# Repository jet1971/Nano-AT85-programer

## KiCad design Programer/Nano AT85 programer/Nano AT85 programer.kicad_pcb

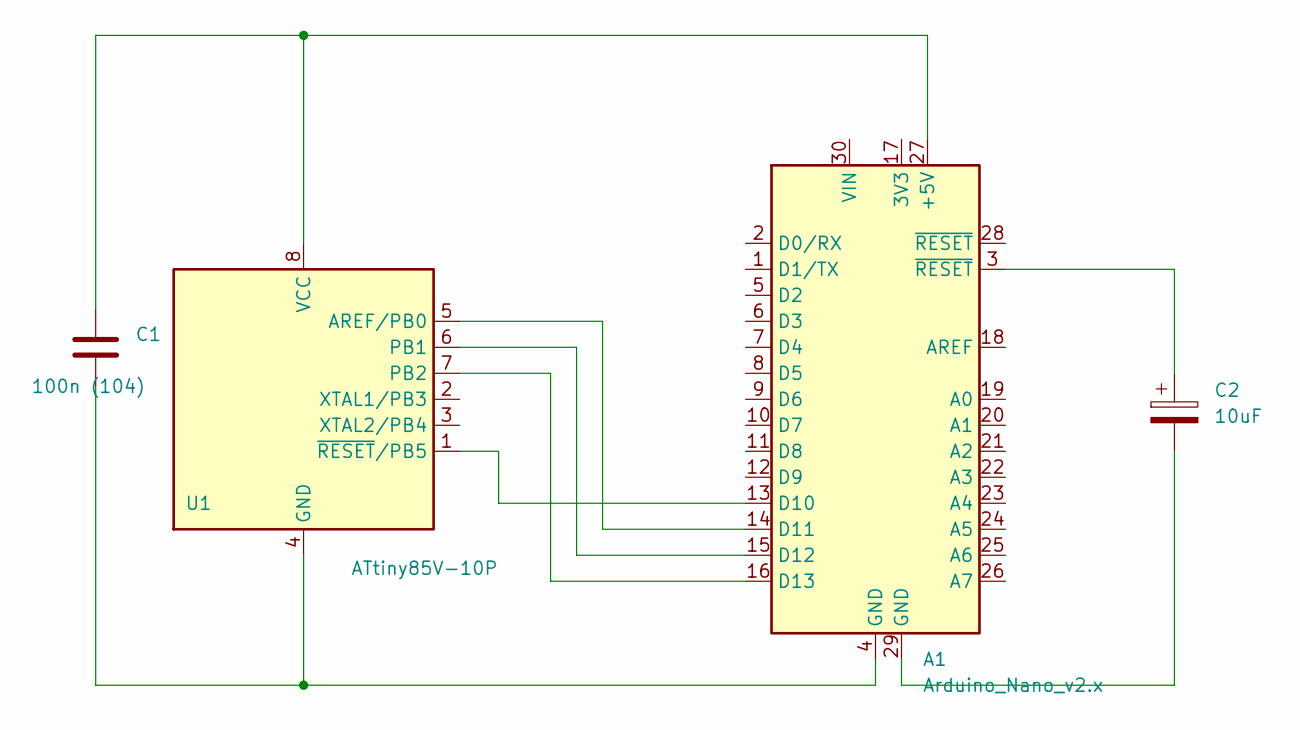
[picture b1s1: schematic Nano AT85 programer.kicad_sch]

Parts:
A1: Arduino_Nano_v2.x; Arduino_Nano
C1: 100n (104); C_Disc_D4.7mm_W2.5mm_P5.00mm
C2: 10uF; CP_Radial_D6.3mm_P2.50mm
U1: ATtiny85V-10P; DIP-8_W7.62mm

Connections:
unnamed: A1.3 (~RESET), C2.1
unnamed: A1.4 (GND), C1.2, U1.4 (GND)
unnamed: A1.13 (D10), U1.1 (~RESET/PB5)
unnamed: A1.14 (D11), U1.5 (AREF/PB0)
unnamed: A1.15 (D12), U1.6 (PB1)
unnamed: A1.16 (D13), U1.7 (PB2)
unnamed: A1.27 (+5V), C1.1, U1.8 (VCC)
unnamed: A1.29 (GND), C2.2

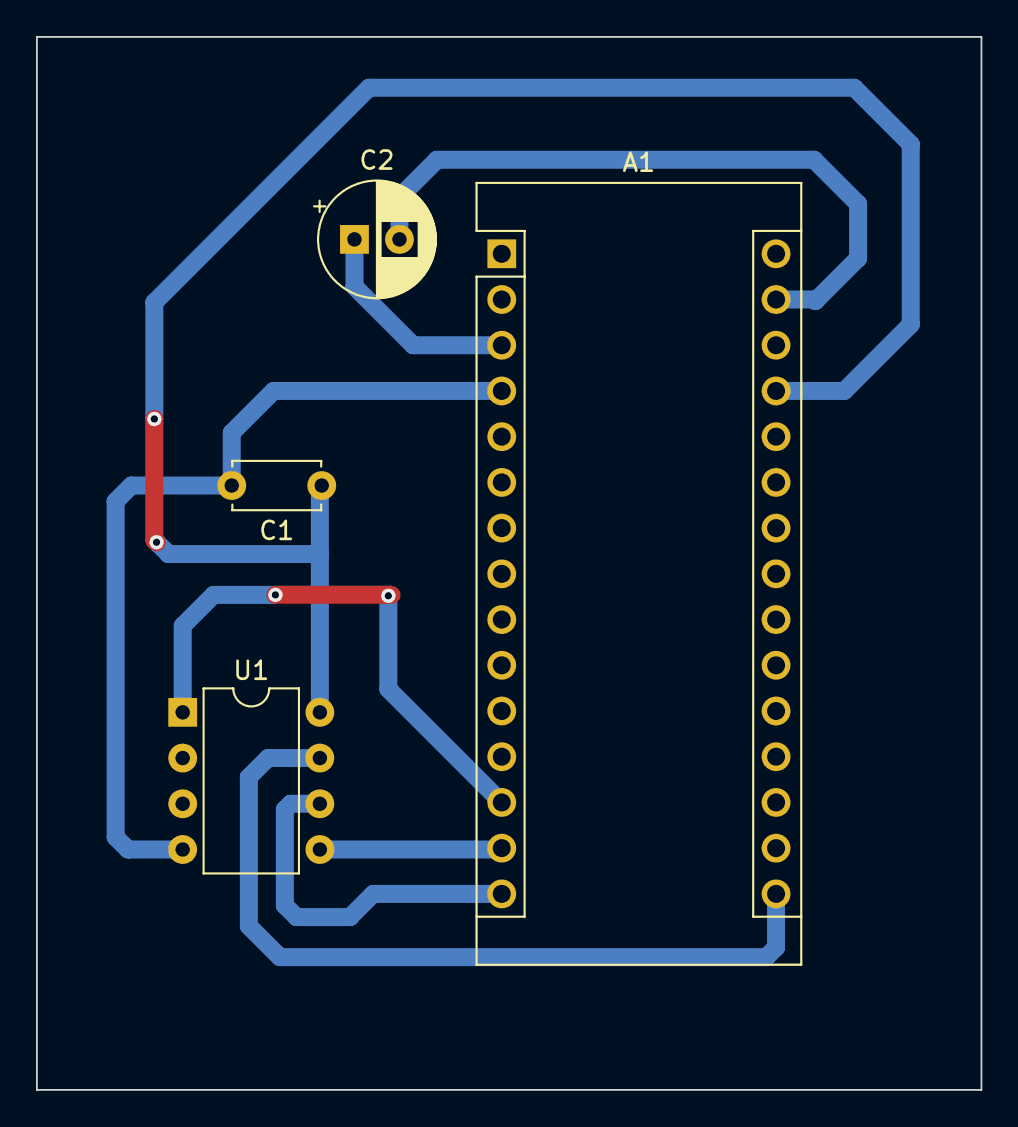
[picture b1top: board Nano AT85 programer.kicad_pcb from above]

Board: 2 copper layers, 52.5 x 58.5 mm, 4 parts (0 on the bottom side), 8 nets.

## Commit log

2022-09-04 Nano AT85 programer
2022-09-04 Values added
2022-09-04 stuff git push
    git stsatu
    git status
    ''jjj
